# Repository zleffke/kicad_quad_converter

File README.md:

# kicad_quad_converter
Quadrature Encoder Level Converter, part of rotator controller project

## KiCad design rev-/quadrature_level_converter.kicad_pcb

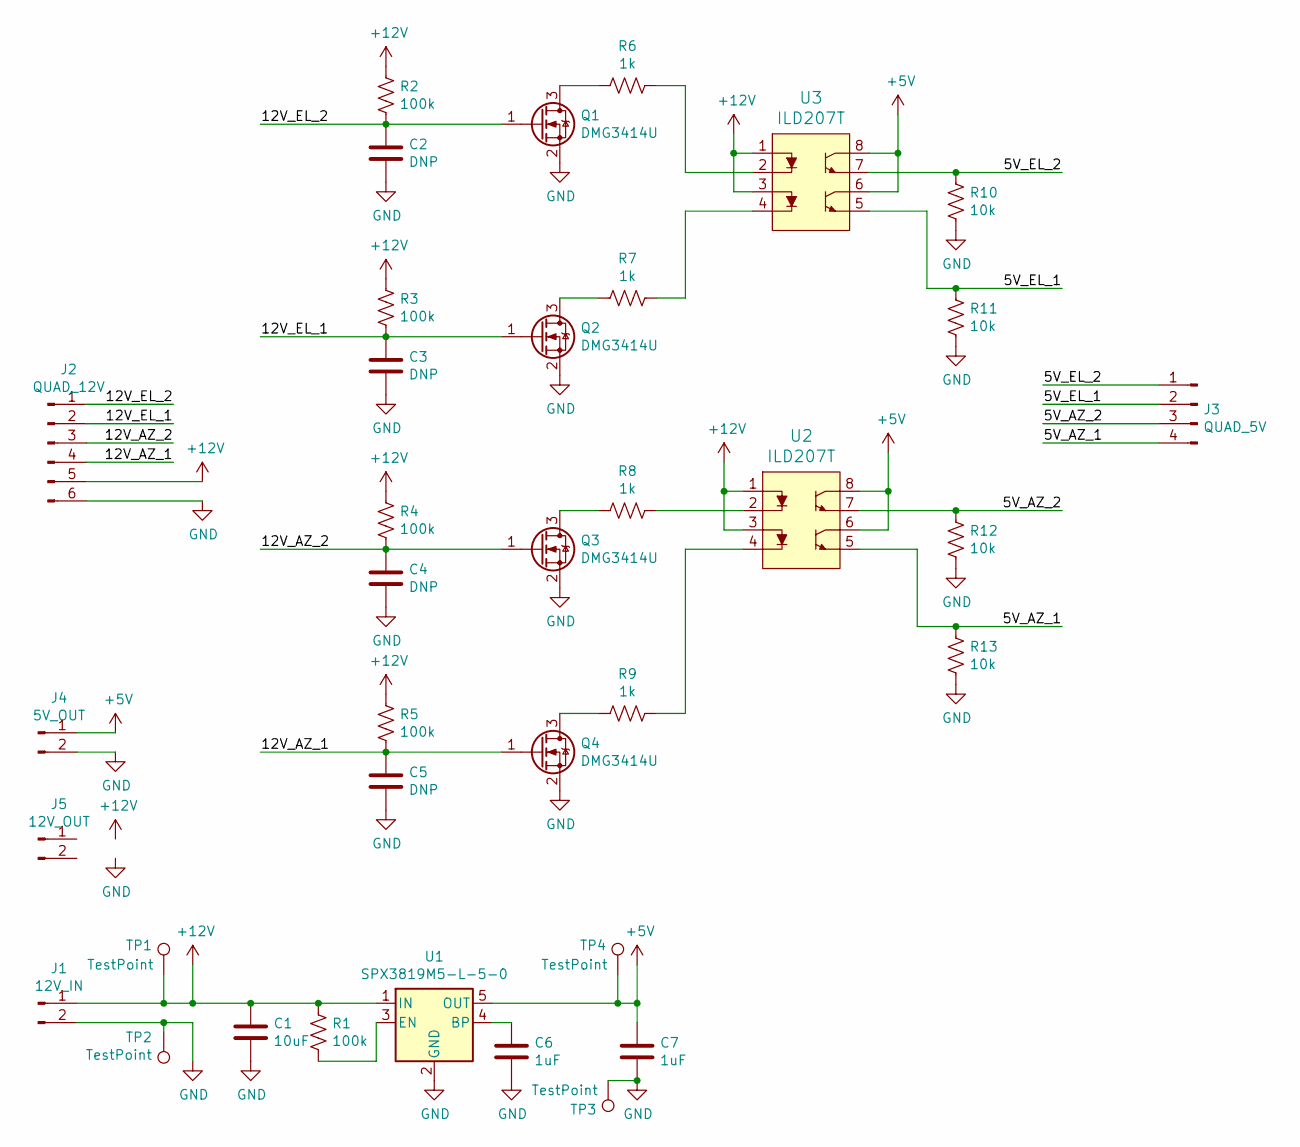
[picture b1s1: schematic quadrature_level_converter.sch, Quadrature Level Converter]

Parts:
C1: 10uF; 0805
C2, C3, C4, C5: DNP; 0805
C6, C7: 1uF; 0805
J1: 12V_IN; PinHeader_1x02_P2.54mm_Vertical
J2: QUAD_12V; PinHeader_1x06_P2.54mm_Vertical
J3: QUAD_5V; PinHeader_1x04_P2.54mm_Vertical
J4: 5V_OUT; PinHeader_1x02_P2.54mm_Vertical
J5: 12V_OUT; PinHeader_1x02_P2.54mm_Vertical
Q1, Q2, Q3, Q4: DMG3414U; SOT-23
R1, R2, R3, R4, R5: 100k; 0805
R6, R7, R8, R9: 1k; 0805
R10, R11, R12, R13: 10k; 0805
TP1, TP2, TP3, TP4: TestPoint; TestPoint_Pad_D4.0mm
U1: SPX3819M5-L-5-0; SOT-23-5
U2, U3: ILD207T; SOIC-8_W3.9mm; MPN ILD207T; Digi-Key_PN 751-1310-1-ND

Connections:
+5V: C7.1, J4.1, TP4.1, U1.5 (OUT), U2.6, U2.8, U3.6, U3.8
+12V: C1.1, J1.1, J2.5, R1.2, R2.1, R3.1, R4.1, R5.1, TP1.1, U1.1 (IN), U2.1, U2.3, U3.1, U3.3
/5V_AZ_1: J3.4, R13.1, U2.5
/5V_AZ_2: J3.3, R12.1, U2.7
/5V_EL_1: J3.2, R11.1, U3.5
/5V_EL_2: J3.1, R10.1, U3.7
/12V_AZ_1: C5.1, J2.4, Q4.1 (G), R5.2
/12V_AZ_2: C4.1, J2.3, Q3.1 (G), R4.2
/12V_EL_1: C3.1, J2.2, Q2.1 (G), R3.2
/12V_EL_2: C2.1, J2.1, Q1.1 (G), R2.2
GND: C1.2, C2.2, C3.2, C4.2, C5.2, C6.2, C7.2, J1.2, J2.6, J4.2, Q1.2 (S), Q2.2 (S), Q3.2 (S), Q4.2 (S), R10.2, R11.2, R12.2, R13.2, TP2.1, TP3.1, U1.2 (GND)
unnamed: C6.1, U1.4 (BP)
unnamed: Q1.3 (D), R6.2
unnamed: Q2.3 (D), R7.2
unnamed: Q3.3 (D), R8.2
unnamed: Q4.3 (D), R9.2
unnamed: R1.1, U1.3 (EN)
unnamed: R6.1, U3.2
unnamed: R7.1, U3.4
unnamed: R8.1, U2.2
unnamed: R9.1, U2.4

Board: 2 copper layers, 36 parts (0 on the bottom side), 21 nets, no tracks yet.

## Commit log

2021-02-22 mass commit

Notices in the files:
rev-/quadrature_level_converter.sch:
creativecommons.org/licenses/by/4.0
License: CC BY 4.0
